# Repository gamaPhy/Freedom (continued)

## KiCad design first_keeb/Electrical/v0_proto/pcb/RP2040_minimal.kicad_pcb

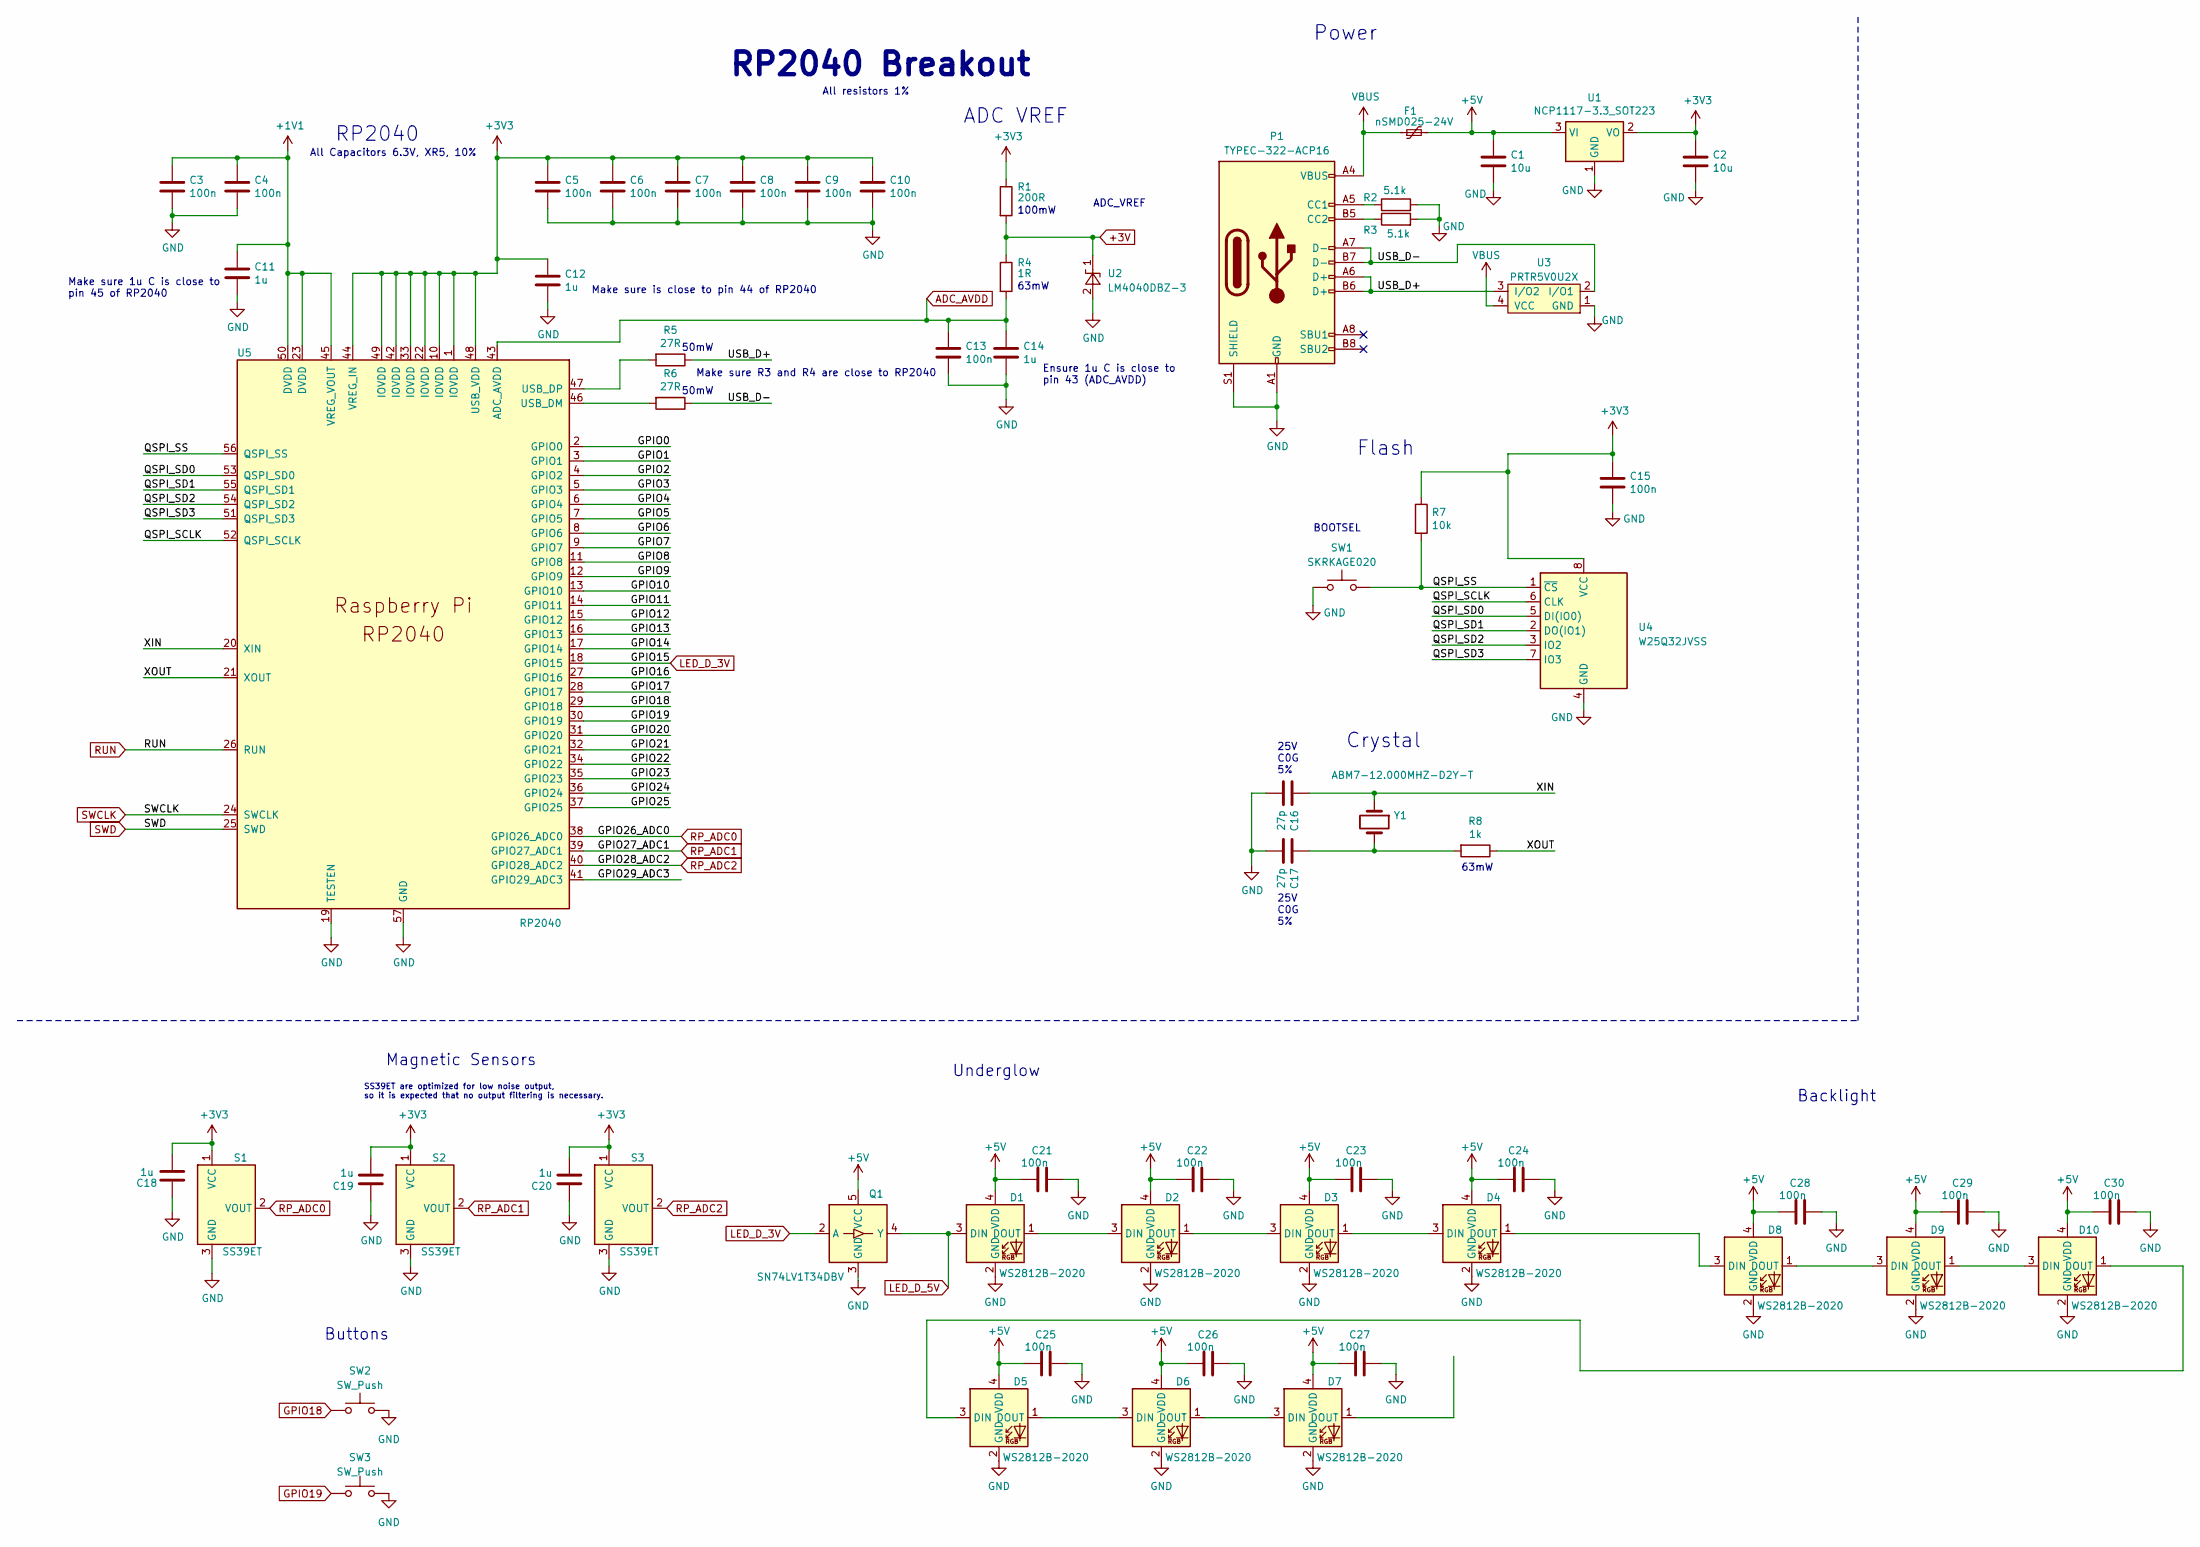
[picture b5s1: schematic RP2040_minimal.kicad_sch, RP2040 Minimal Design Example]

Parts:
C1, C2: 10u; C_0805_2012Metric
C3, C4, C5, C6, C7, C8, C9, C10, C13, C15, C21, C22, C23, C24, C25, C26, C27, C28, C29, C30: 100n; C_0402_1005Metric
C11, C12, C14, C18, C19, C20: 1u; C_0402_1005Metric
C16, C17: 27p; C_0402_1005Metric
D1, D2, D3, D4, D5, D6, D7, D8, D9, D10: WS2812B-2020; LED_WS2812B-2020_PLCC4_2.0x2.0mm
F1: nSMD025-24V; Fuse_1206_3216Metric
P1: TYPEC-322-ACP16; USB_C_Receptacle_GCT_USB4105-xx-A_16P_TopMnt_Horizontal
Q1: SN74LV1T34DBV; SOT-23-5
R1: 200R; C_0603_1608Metric
R2, R3: 5.1k; C_0402_1005Metric
R4: 1R; C_0603_1608Metric
R5, R6: 27R; C_0402_1005Metric
R7: 10k; C_0402_1005Metric
R8: 1k; C_0402_1005Metric
S1, S2, S3: SS39ET; SOT-23-3
SW1: SKRKAGE020; SW_Push_SPST_NO_Alps_SKRK
SW2, SW3: SW_Push; SW_Push_1P1T_NO_6x6mm_H9.5mm
U1: NCP1117-3.3_SOT223; SOT-223-3_TabPin2
U2: LM4040DBZ-3; SOT-23
U3: PRTR5V0U2X; SOT-143B
U4: W25Q32JVSS; SOIC-8_5.23x5.23mm_P1.27mm
U5: RP2040; RP2040-QFN-56
Y1: ABM7-12.000MHZ-D2Y-T; Crystal_SMD_Abracon_ABM7-2Pin_6.0x3.5mm

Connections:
+1V1: C3.1, C4.1, C11.1, U5.23 (DVDD), U5.45 (VREG_VOUT), U5.50 (DVDD)
+3V: R1.2, R4.1, U2.1 (K)
+3V3: C2.1, C5.1, C6.1, C7.1, C8.1, C9.1, C10.1, C12.1, C15.1, C18.2, C19.2, C20.2, R1.1, R7.1, S1.1 (VCC), S2.1 (VCC), S3.1 (VCC), U1.2 (VO), U4.8 (VCC), U5.1 (IOVDD), U5.10 (IOVDD), U5.22 (IOVDD), U5.33 (IOVDD), U5.42 (IOVDD), U5.44 (VREG_IN), U5.48 (USB_VDD), U5.49 (IOVDD)
+5V: C1.1, C21.1, C22.1, C23.1, C24.1, C25.1, C26.1, C27.1, C28.1, C29.1, C30.1, D1.4 (VDD), D2.4 (VDD), D3.4 (VDD), D4.4 (VDD), D5.4 (VDD), D6.4 (VDD), D7.4 (VDD), D8.4 (VDD), D9.4 (VDD), D10.4 (VDD), F1.2, Q1.5 (VCC), U1.3 (VI)
/GPIO0: U5.2 (GPIO0)
/GPIO1: U5.3 (GPIO1)
/GPIO2: U5.4 (GPIO2)
/GPIO3: U5.5 (GPIO3)
/GPIO4: U5.6 (GPIO4)
/GPIO5: U5.7 (GPIO5)
/GPIO6: U5.8 (GPIO6)
/GPIO7: U5.9 (GPIO7)
/GPIO8: U5.11 (GPIO8)
/GPIO9: U5.12 (GPIO9)
/GPIO10: U5.13 (GPIO10)
/GPIO11: U5.14 (GPIO11)
/GPIO12: U5.15 (GPIO12)
/GPIO13: U5.16 (GPIO13)
/GPIO14: U5.17 (GPIO14)
/GPIO16: U5.27 (GPIO16)
/GPIO17: U5.28 (GPIO17)
/GPIO20: U5.31 (GPIO20)
/GPIO21: U5.32 (GPIO21)
/GPIO22: U5.34 (GPIO22)
/GPIO23: U5.35 (GPIO23)
/GPIO24: U5.36 (GPIO24)
/GPIO25: U5.37 (GPIO25)
/GPIO29_ADC3: U5.41 (GPIO29_ADC3)
/QSPI_SCLK: U4.6 (CLK), U5.52 (QSPI_SCLK)
/QSPI_SD0: U4.5 (DI(IO0)), U5.53 (QSPI_SD0)
/QSPI_SD1: U4.2 (DO(IO1)), U5.55 (QSPI_SD1)
/QSPI_SD2: U4.3 (IO2), U5.54 (QSPI_SD2)
/QSPI_SD3: U4.7 (IO3), U5.51 (QSPI_SD3)
/QSPI_SS: R7.2, SW1.2, U4.1 (~CS), U5.56 (QSPI_SS)
/USB_D+: P1.A6 (D+), P1.B6 (D+), R5.1, U3.3 (I/O2)
/USB_D-: P1.A7 (D-), P1.B7 (D-), R6.1, U3.2 (I/O1)
/XIN: C16.1, U5.20 (XIN), Y1.1
/XOUT: R8.1, U5.21 (XOUT)
ADC_AVDD: C13.1, C14.1, R4.2, U5.43 (ADC_AVDD)
GND: C1.2, C2.2, C3.2, C4.2, C5.2, C6.2, C7.2, C8.2, C9.2, C10.2, C11.2, C12.2, C13.2, C14.2, C15.2, C16.2, C17.2, C18.1, C19.1, C20.1, C21.2, C22.2, C23.2, C24.2, C25.2, C26.2, C27.2, C28.2, C29.2, C30.2, D1.2 (GND), D2.2 (GND), D3.2 (GND), D4.2 (GND), D5.2 (GND), D6.2 (GND), D7.2 (GND), D8.2 (GND), D9.2 (GND), D10.2 (GND), P1.A1 (GND), P1.A12 (GND), P1.B1 (GND), P1.B12 (GND), P1.S1 (SHIELD), Q1.3 (GND), R2.2, R3.2, S1.3 (GND), S2.3 (GND), S3.3 (GND), SW1.1, SW2.2, SW3.2, U1.1 (GND), U2.2 (A), U3.1 (GND), U4.4 (GND), U5.19 (TESTEN), U5.57 (GND)
GPIO18: SW2.1, U5.29 (GPIO18)
GPIO19: SW3.1, U5.30 (GPIO19)
LED_D_3V: Q1.2 (A), U5.18 (GPIO15)
LED_D_5V: D1.3 (DIN), Q1.4 (Y)
unnamed: C17.1, R8.2, Y1.2
unnamed: D1.1 (DOUT), D2.3 (DIN)
unnamed: D2.1 (DOUT), D3.3 (DIN)
unnamed: D3.1 (DOUT), D4.3 (DIN)
unnamed: D4.1 (DOUT), D8.3 (DIN)
unnamed: D5.1 (DOUT), D6.3 (DIN)
unnamed: D6.1 (DOUT), D7.3 (DIN)
unnamed: D8.1 (DOUT), D9.3 (DIN)
unnamed: D9.1 (DOUT), D10.3 (DIN)
unnamed: D5.3 (DIN), D10.1 (DOUT)
unnamed: P1.A5 (CC1), R2.1
unnamed: P1.B5 (CC2), R3.1
unnamed: R6.2, U5.46 (USB_DM)
unnamed: R5.2, U5.47 (USB_DP)
RP_ADC0: S1.2 (VOUT), U5.38 (GPIO26_ADC0)
RP_ADC1: S2.2 (VOUT), U5.39 (GPIO27_ADC1)
RP_ADC2: S3.2 (VOUT), U5.40 (GPIO28_ADC2)
RUN: U5.26 (RUN)
SWCLK: U5.24 (SWCLK)
SWD: U5.25 (SWD)
VBUS: F1.1, P1.A4 (VBUS), P1.A9 (VBUS), P1.B4 (VBUS), P1.B9 (VBUS), U3.4 (VCC)

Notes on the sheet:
RP2040 Breakout
All Capacitors 6.3V, XR5, 10%
Make sure 1u C is close to pin 45 of RP2040
ADC VREF
63mW
25V C0G 5%
ADC_VREF
Make sure R3 and R4 are close to RP2040
Magnetic Sensors
Underglow
RP2040
SS39ET are optimized for low noise output, so it is expected that no output filtering is necessary.
BOOTSEL
Power
Buttons
Crystal
Make sure is close to pin 44 of RP2040
All resistors 1%
Backlight
50mW
Flash
Ensure 1u C is close to pin 43 (ADC_AVDD)
100mW

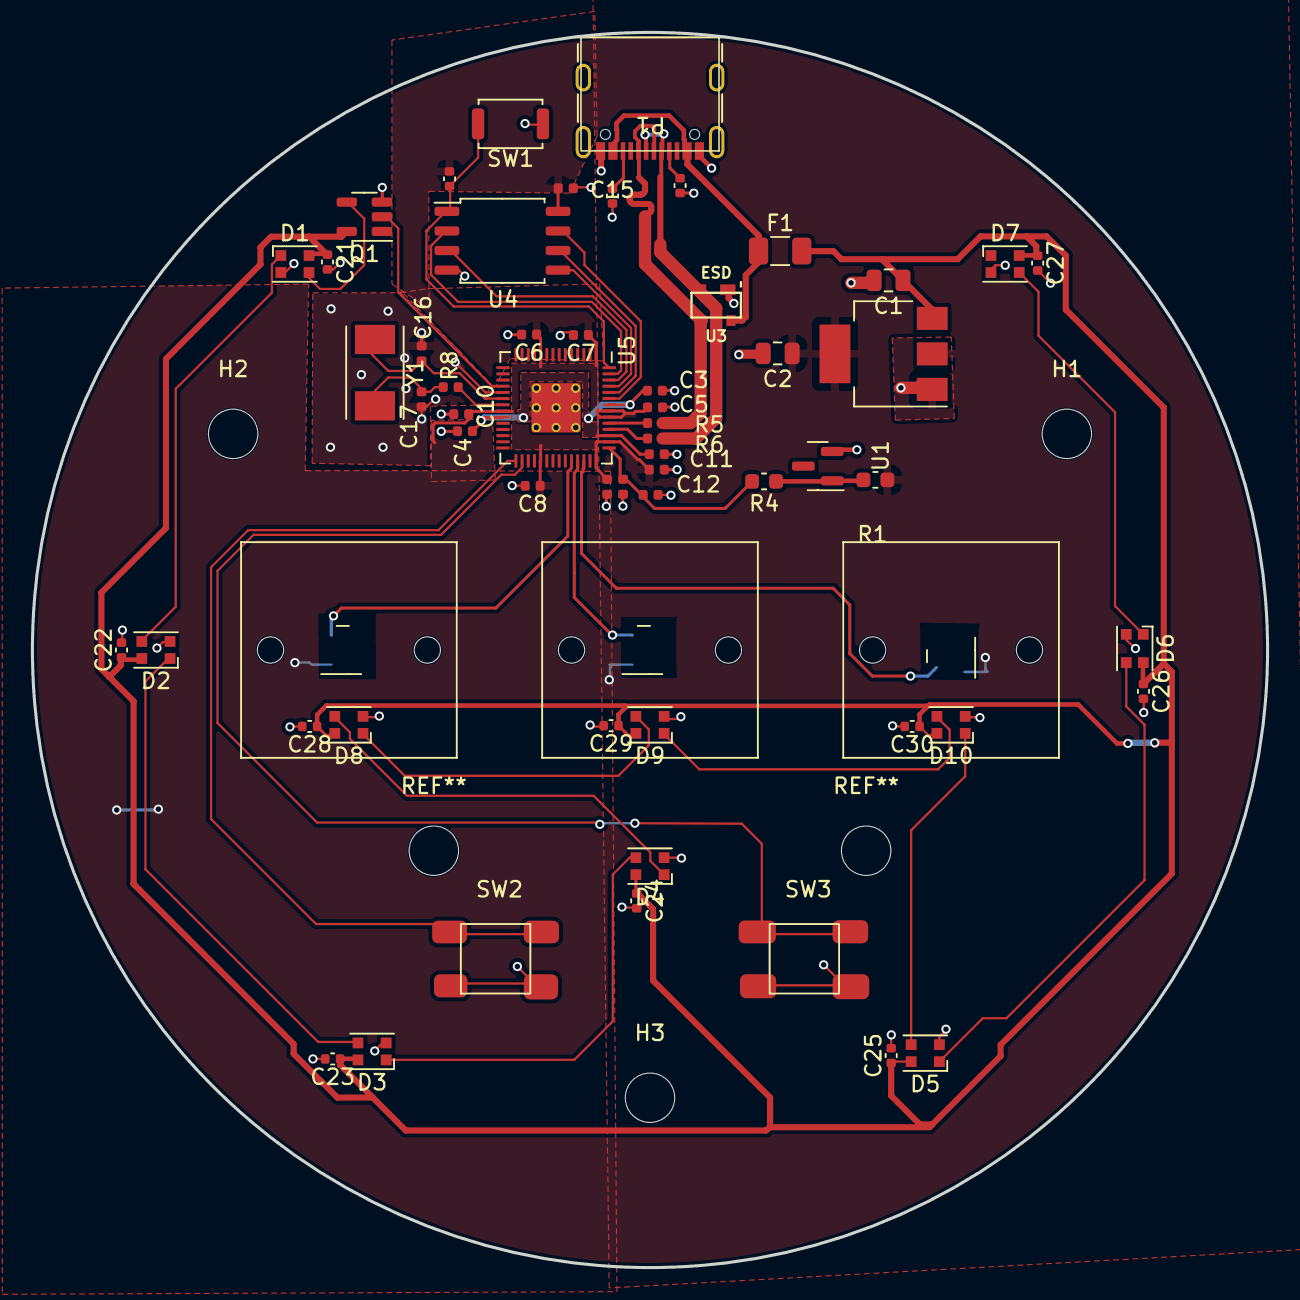
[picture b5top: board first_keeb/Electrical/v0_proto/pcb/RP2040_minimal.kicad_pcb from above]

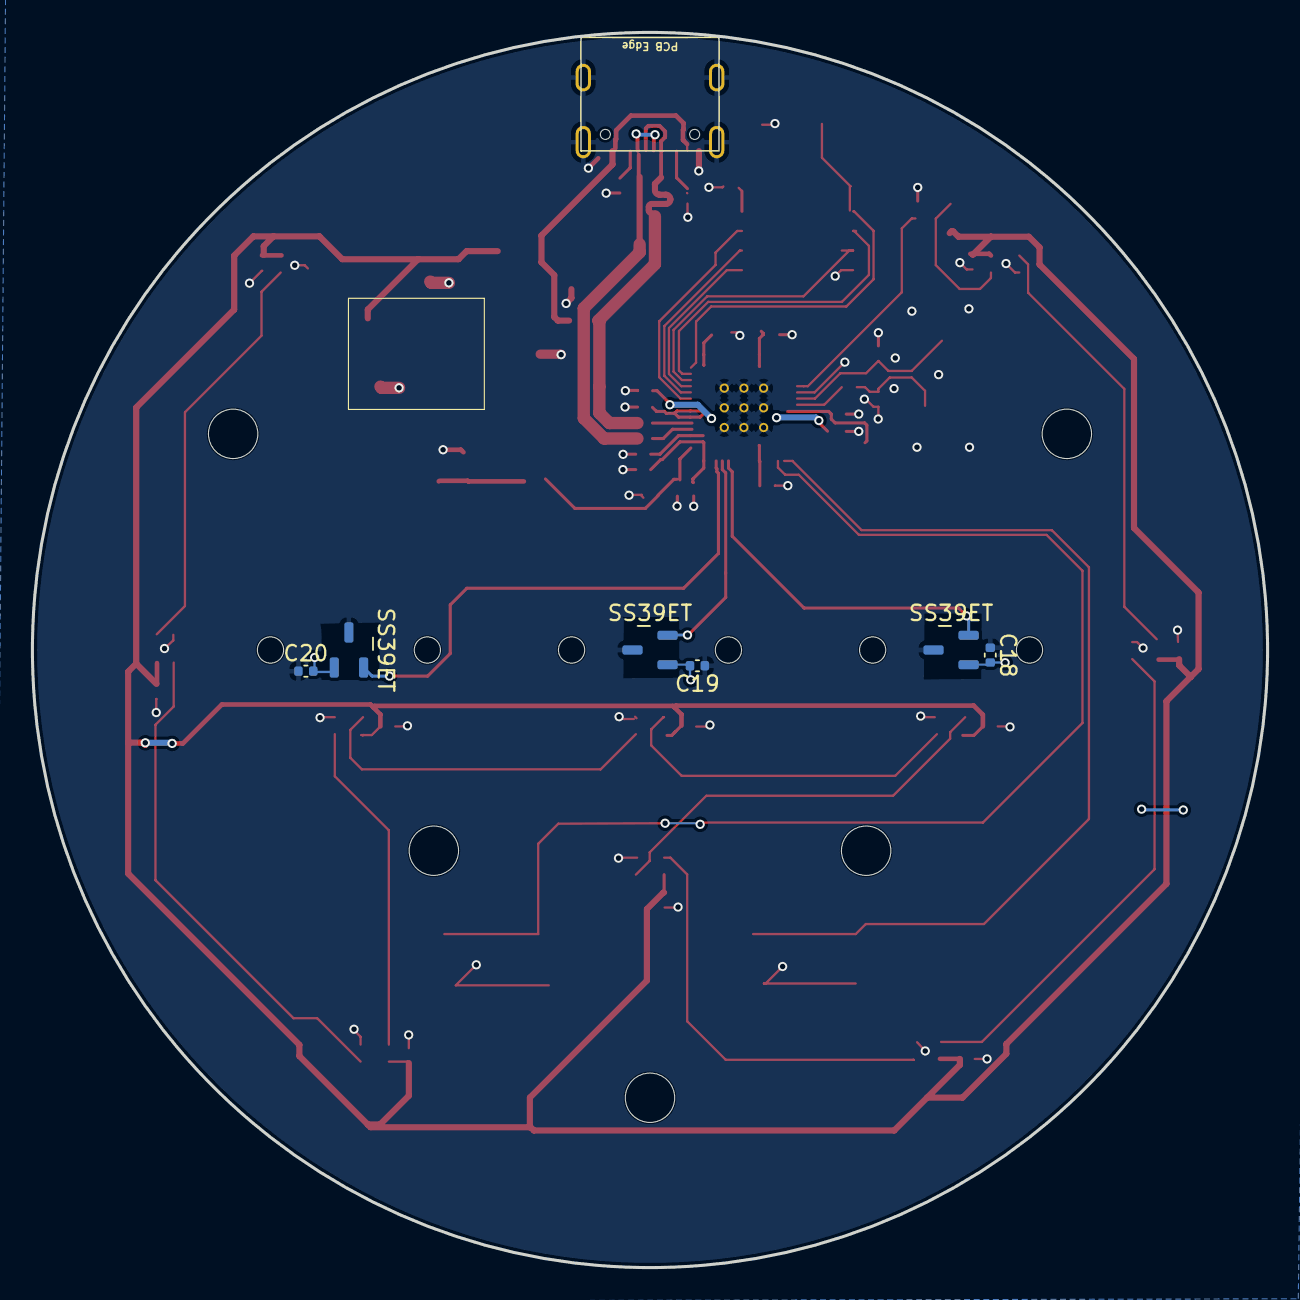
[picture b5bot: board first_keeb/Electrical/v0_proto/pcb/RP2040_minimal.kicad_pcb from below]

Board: 2 copper layers, 80.0 x 80.0 mm, 66 parts (6 on the bottom side), 38 nets.

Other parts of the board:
H1, H2, H3: MountingHole_3.2mm_M3

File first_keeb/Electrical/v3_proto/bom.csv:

"Comment All resistor at least 1%, and >=100mW All capacitor at least 5%, and >= 6.3 V ",Designator,Footprint
10uF,"C1, C2",Capacitor_SMD:C_0805_2012Metric
100nF,"C3, C4, C5, C6, C7, C8, C9, C10, C13, C15",Capacitor_SMD:C_0402_1005Metric
1uF,"C11, C12, C14, C16, C19, C20, C21, C22, C23, C24, C25, C26, C27, C28",Capacitor_SMD:C_0402_1005Metric
27pF,"C17, C18",Capacitor_SMD:C_0402_1005Metric
WS2812B,"D1, D2, D3, D4",LED_SMD:LED_WS2812B_PLCC4_5.0x5.0mm_P3.2mm
0ZCJ0025AF2E,F1,Fuse:Fuse_1206_3216Metric
USB4105-GF-A,P1,Connector_USB:USB_C_Receptacle_GCT_USB4105-xx-A_16P_TopMnt_Horizontal
BSS138,Q1,Package_TO_SOT_SMD:SOT-23
200 Ohm,R1,Capacitor_SMD:C_0603_1608Metric
5.1k,"R2, R3",Capacitor_SMD:C_0402_1005Metric
1 Ohm,R4,Capacitor_SMD:C_0603_1608Metric
27 Ohm ,"R5, R6",Capacitor_SMD:C_0402_1005Metric
10k,"R7, R9, R10",Capacitor_SMD:C_0402_1005Metric
1k,R8,Capacitor_SMD:C_0402_1005Metric
SS39ET,"S1, S2, S3",Package_TO_SOT_SMD:SOT-23-3
NCP1117-3.3_SOT223,U1,Package_TO_SOT_SMD:SOT-223-3_TabPin2
LM4040DBZ-3,U2,Package_TO_SOT_SMD:SOT-23
PRTR5V0U2X,U3,Package_TO_SOT_SMD:SOT-143
W25Q32JVSS,U4,Package_SO:SOIC-8_5.23x5.23mm_P1.27mm
RP2040,U5,RP2040_minimal:RP2040-QFN-56
ABM7-12.000MHZ-D2Y-T,Y1,Crystal:Crystal_SMD_Abracon_ABM7-2Pin_6.0x3.5mm

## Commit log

2023-02-21 not bad
2023-02-21 change dir name
2023-02-21 add MCU, i2c pullup, and oled to sch
2023-02-21 save the sch
2023-02-21 fixes i2c and moves them to gpio that can only do i2c. Adds pico pinout picture
2023-02-21 fix dotted lines
2023-02-21 add todos for electrical
2023-02-22 adds jumper configuration to select any voltage source for testing purposes
2023-02-22 improve jumper config circuit
2023-02-22 adds a lot of new things to schematic
2023-02-22 ready to start frist pcb
2023-02-23 finish v1 pcb, and generate drill file+plot
2023-02-23 adds right angle switch to pcb and plots gerbers
2023-02-23 zip first gerbers
2023-02-23 improve pcb
2023-02-23 add gnd pour on back layer
2023-02-23 fixes gnd plane issues on pcb
2023-02-23 fix ground plane issues
2023-02-23 remove unused via to gnd
2023-02-23 actual v1
2023-02-23 Basic firmware
2023-02-23 Add comments
2023-02-23 move OLED update loop to its own core and display Hz on OLED
2023-02-23 increase polling rate from 250 to 1000 Hz
2023-02-23 create firmware todo
2023-02-24 adds web serial to todo
2023-02-24 changes buttons to active low
2023-02-25 add settings, menu, 2 extra buttons, and flash storage
2023-02-25 implement rgb modes
2023-02-25 update firmware todo
2023-02-25 fix the edgiest case and refactor inputs
2023-02-26 gpio 0 boots into bootsel mode
2023-02-27 basic qmk firmware
2023-02-28 lays out all non-gpio connections to rp2040
2023-02-28 script for recovering staged local changes I accidentally delete when running `git reset --hard` instead of `git reset --soft`. The script can only retrieve changes that were staged or commited.
2023-03-01 finishes pcb except for the test points.
2023-03-01 finishes proto_2 pcb
2023-03-01 moves vbus away from pads
2023-03-01 ads voltage reference
2023-03-01 generate gerbers
2023-03-02 finishes proto_v2 board. Set up some stuff to automate jlcpcb format for pcb assembly
2023-03-02 make groupings template
2023-03-04 finishes circular pcb
2023-03-04 finishes pcb even more
2023-03-04 ads bootsel button and changes pcb to 80mm diameter
2023-03-04 implement analog scanning and settings changing
2023-03-04 ads threaded mounting hole
2023-03-04 Update readme.md
    update bootsel button instructions
2023-03-04 ordered pcb assembly
2023-03-05 adds mecahnical stuff
2023-03-05 adds case part mechanical
2023-03-05 step file
2023-03-05 adds saving settings and changing settings thru VIA
2023-03-05 finish proto_v4 pcb
2023-03-05 removes extra led
2023-03-05 makes 3v3 pour have more access
2023-03-06 first prototype of case
2023-03-06 adds stl file
2023-03-06 adds freecad gitignore
2023-03-06 adds VIA custom keycodes
2023-03-07 v1 pcb with backlights and underglow. started case designs
2023-03-07 v1 of case
2023-03-08 add 3d print settings
2023-03-08 refactor matrix scanning to allow for analog keys anywhere
2023-03-08 implement rapid trigger sensitivity
2023-03-08 add sensitivity setting to VIA
2023-03-08 makes countersink on bottom of case pi/4 rad, and starts the plate
2023-03-08 add more 3d printing settings
2023-03-09 refactor everything so different keypads are easy to create
2023-03-10 creates a board that uses mid-mount usbc receptacle, and has all the rp2040 circuitry on the opposite layer of keyboard switches so that foam mod can be made easily. Also adds the threaded inserts
2023-03-10 make room for weights under pcb lower half
2023-03-11 adds another option for pcb with threaded insert
2023-03-12 v1 case and pcb complete
2023-03-12 add usbc cable slot into case
2023-03-12 update readme file
2023-03-12 case with mid mount
2023-03-12 have top mount, and mid mount receptacle cases
2023-03-12 remove sharp edge from usbc cable hole
2023-03-12 saving case
2023-03-13 added the techstack
2023-03-13 add printing profile and some test printing stuff
2023-03-15 adds 2 layer and 4 layer pcb versions
2023-03-15 improve 3v3 traces in 2 layer board
2023-03-15 improve d+/d- traces
2023-03-17 remove unused prototype boards
2023-03-17 move stuff around
2023-03-17 Update README.md
    Add integral info
2023-03-18 add leds and fix rapid trigger
2023-03-18 changing some proto v0 stuff
2023-03-22 stm it up
2023-03-24 stm32 pcb almost done
2023-03-25 vcc pour and ground
2023-03-25 adds leds
2023-03-25 create vdd traces instead of pour
2023-03-25 finishes pcb v1 with smaller radius
2023-03-25 cleanup tracks and vias
2023-03-25 improve power routing to go around analog signals
2023-03-25 generate prod files for pcb
2023-03-26 fixes lcsc number in bom
2023-03-26 adds basic part switch
2023-03-27 creates plate for pcb
2023-03-28 - no more tan caps - adds 1u before ferrite - ties ties other side of boot0 resistor to gnd
2023-03-28 fix mag sensor schematic
2023-03-28 add svg
2023-03-28 adds pdf
2023-03-31 stm fixes, still has different voltages
2023-04-01 changes to ws2812b 5050 and moves 5v power rail to mostly 4th layer
2023-04-05 v1 stm ordered
2023-04-07 updates pcb
2023-04-10 no more line in 3d print
2023-04-13 moves pcb components down to make more space, and fixes case
2023-04-13 adds cura slicer profile used for case
2023-04-17 update firmware to stm32f401
2023-04-17 invert polarity in firmware
2023-04-17 adds oversampling removing outliers
2023-04-23 finishes stm with 3d printed standoff holes
2023-04-23 create separate folders for rp2040 and stm32 designs
2023-04-23 removes unused projects
2023-04-23 finishes rp2040 v1
2023-04-23 switches swdio and swclk on stm to match rp2040
2023-04-23 adds 10n and 100n capactiros near rp2040 adc_avdd
2023-04-23 puts 10n and 1u caps to decouple adv_avdd on rp2040 to match the stm32 adc vref
2023-04-23 generates assembly files
2023-04-23 make bottom hole
2023-04-23 adds silkscreen to stm32 buttons
2023-04-23 moves plates together
2023-04-23 changes caps to match 12MHz crystal
2023-04-23 adds pullup for run pin
2023-04-23 repo cleanup
2023-04-23 more cleanup
2023-04-24 fixes rp2040 board, stm32 board still todo
2023-04-25 Move firmware to https://github.com/gamaPhy/qmk-keyboards
2023-04-27 case v0
2023-04-27 adds small moat to case to prevent line from forming on outside of case when 3d printed.
2023-04-27 fixes case heights and makes the final case
2023-04-28 creates 3mf 3d print config files for case
2023-04-28 improves component placement
2023-04-28 adds gnd vias near connector
2023-05-08 improves case and pcb
2023-07-01 creates outline with screw and 3d printed standoffs, and space for panelization mousebites to be put for better case fit.
2023-07-02 finishes new pcb edge cuts
2023-07-02 prod files
2023-07-02 adds stitching vias
2023-07-02 update plate holes
2023-07-03 adds lscs num for resistor
2023-07-03 improves location of HE decoupling caps
2023-07-03 adds more stitching vias
2023-07-14 updates case
2023-07-14 moves standoffs
2023-07-14 makes case files more robust
2023-07-14 adds screw holes to stabilize pcb
2023-07-14 improves location of pcb stabilizing screws
2023-07-16 creates 3mf with supports that are easier to remove
2023-07-18 creates LICENSE
2023-07-18 Update LICENSE
2023-07-18 addslink to firmware for Freedom series keypads
2023-07-18 Adds image of Freedom-3k to README
2023-07-18 make image smaller
2023-07-18 make image even smaller
2023-08-04 Removes broken image link from README.md
2023-09-28 removes unused dir
2023-10-07 uses backlight to refer to individual key lights, and underglow for the rest
2023-10-08 saves latest progress
2023-10-09 finishes rp2040 2 layer board with split gnd
2023-10-31 finishes 4 layer split gnd rp2040 board. tested and saw that noise is worse with split gnd when compared to connected GND
2023-12-04 adds comments for mousebite locations and changes via stitching spacing to 2.54mm
2023-12-04 removes all power supplies except 3v3 and moves some things around in schematic
2023-12-07 add HE sensor keepout zone to all layers
2023-12-07 adds 3v3 pour for analog stuff
2023-12-07 improve 3v3 pour for analog stuff
2024-03-10 adds all circuit components needed for final pcb, but may need more LED
2024-03-11 reverts to using standard bs138 because the dual package one is more expensive than just using two of them, and it's easier to layout
2024-03-11 places perkey backlight leds
2024-03-11 adds buttons
2024-03-11 adds 2020 led to smoothen out LED diffusing on sides
2024-03-12 adds instructions to readme, adds the button changes to plate
2024-03-21 adds some height to standoffs so that switches sit more comfortably, and changes nut holes to square
2024-03-21 misc updates
2024-03-22 changes led per-key backlights to 2020 and adds more screw holes for tilting issue
2024-03-22 fixes stray via
2024-03-22 puts in more led
2024-03-22 reorient HE sensors
2024-03-22 misc changes
2024-03-22 changes trace width of analog signals to be 0.3
2024-03-22 reorganize some components for better fit
2024-03-22 dodge the screw holes so that the signals never have a chance of touching the metal screws
2024-03-22 finishes PCB layout
2024-03-22 pcb ready for jlc
2024-03-22 adds jlc gerber files
2024-03-22 misc fixes and gen jlc gerber
2024-03-22 removes socket from bom and cpl
2024-03-22 makes all 100nf caps the same one
2024-03-22 changes slss49 to DRV
2024-03-22 finishes pcb
2024-03-22 plate jlc newest gerber
2024-03-22 finishes case for now
2024-03-28 switches back to 1 data pin for LED
2024-03-28 fixes up power traces
